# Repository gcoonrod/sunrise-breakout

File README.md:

# Sunrise Breakout

Breadboard friendly breakout for RGBW LEDs, LP5012, and LM3410.

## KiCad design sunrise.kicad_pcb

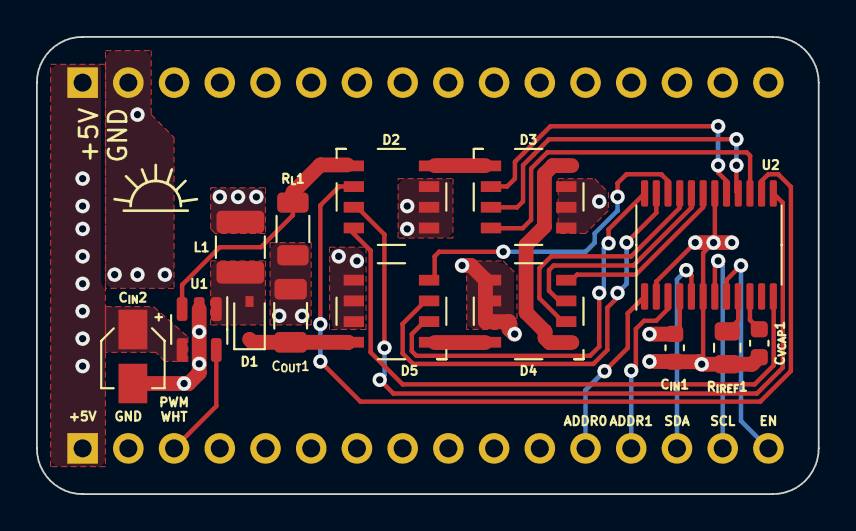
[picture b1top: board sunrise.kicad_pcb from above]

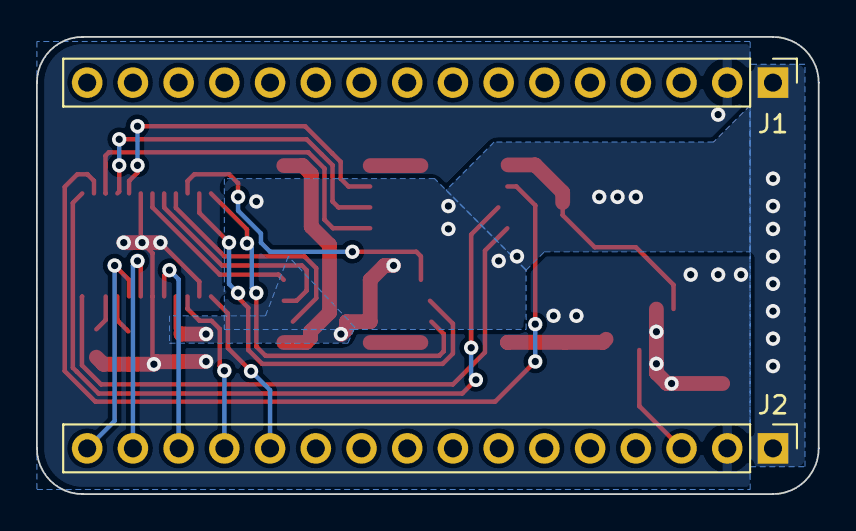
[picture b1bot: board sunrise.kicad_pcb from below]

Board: 2 copper layers, 43.4 x 25.4 mm, 16 parts (2 on the bottom side), 28 nets.

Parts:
C_{IN}1: 1u; C_0603_1608Metric
C_{IN}2: 10u; CP_Elec_3x5.3
C_{OUT}1: 1n2; C_1206_3216Metric
C_{VCAP}1: 1u; C_0603_1608Metric
D1: 30V; D_SOD-323
D2, D3, D4, D5: LED_RGBW; LED_SMD5050-8
J1: TOP_HDR; PinHeader_1x16_P2.54mm_Vertical
J2: BTM_HDR; PinHeader_1x16_P2.54mm_Vertical
L1: 10u; L_1210_3225Metric
R_{IREF}1: 374; R_0805_2012Metric
R_{L}1: 10; R_1206_3216Metric
U1: LM3410; SOT-23-5
U2: LP5012; TSSOP-24_4.4x7.8mm_P0.65mm

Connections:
/ADDR0: J2.12, U2.1 (ADDR0)
/ADDR1: J2.13, U2.3 (ADDR1)
/DIM_WHT: J2.3, U1.5 (DIM)
/FB_WHT: D2.5, R_{L}1.1, U1.3 (FB)
/OUT0: D2.8, U2.12 (OUT0)
/OUT1: D2.7, U2.13 (OUT1)
/OUT2: D2.6, U2.14 (OUT2)
/OUT3: D3.8, U2.15 (OUT3)
/OUT4: D3.7, U2.16 (OUT4)
/OUT5: D3.6, U2.17 (OUT5)
/OUT6: D4.8, U2.19 (OUT6)
/OUT7: D4.7, U2.20 (OUT7)
/OUT8: D4.6, U2.21 (OUT8)
/OUT9: D5.8, U2.22 (OUT9)
/OUT10: D5.7, U2.23 (OUT10)
/OUT11: D5.6, U2.24 (OUT11)
/RGB_EN: J2.16, U2.8 (EN)
/SCL: J2.15, U2.7 (SCL)
/SDA: J2.14, U2.5 (SDA)
/SW_WHT: D1.2 (A), L1.2, U1.1 (SW)
/V_{OUT}_WHT: C_{OUT}1.1, D1.1 (K), D5.4
GND: C_{IN}1.2, C_{IN}2.2, C_{OUT}1.2, C_{VCAP}1.2, J1.2 (GND), J2.2, R_{IREF}1.1, R_{L}1.2, U1.2 (GND), U2.2 (AGND), U2.6 (PGND), U2.18 (DGND)
unnamed: C_{VCAP}1.1, U2.10 (VCAP)
unnamed: D2.4, D3.5
unnamed: D3.4, D4.5
unnamed: D4.4, D5.5
unnamed: R_{IREF}1.2, U2.9 (IREF)
VCC: C_{IN}1.1, C_{IN}2.1, D2.1, D2.2, D2.3, D3.1, D3.2, D3.3, D4.1, D4.2, D4.3, D5.1, D5.2, D5.3, J1.1 (VCC), J2.1, L1.1, U1.4 (VIN), U2.4 (VCC)

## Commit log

2023-01-06 inital commit
2023-01-06 Update RGBW footprint and BOM.
